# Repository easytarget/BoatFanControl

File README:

# Humidity sensor and fan controller for a small boat
## By Owen.

* DigiSpark Based
 * ATTiny 85
 * Has a onboard 5v regulator
 * 6 IO pins.. very little extra cruft
 * Somewhat tricky to flash/develop for, Lack of a uart is a total pain during debug.
* PWM fan control via a mosfet
* Battery voltage sensing for powersave and shutdown
* A button.. to allow on/off/quiet, etc.
* DHT11 Temperature and Humidity sensor
 * Not ideal, something more accurate would be prefered but this is what I have,

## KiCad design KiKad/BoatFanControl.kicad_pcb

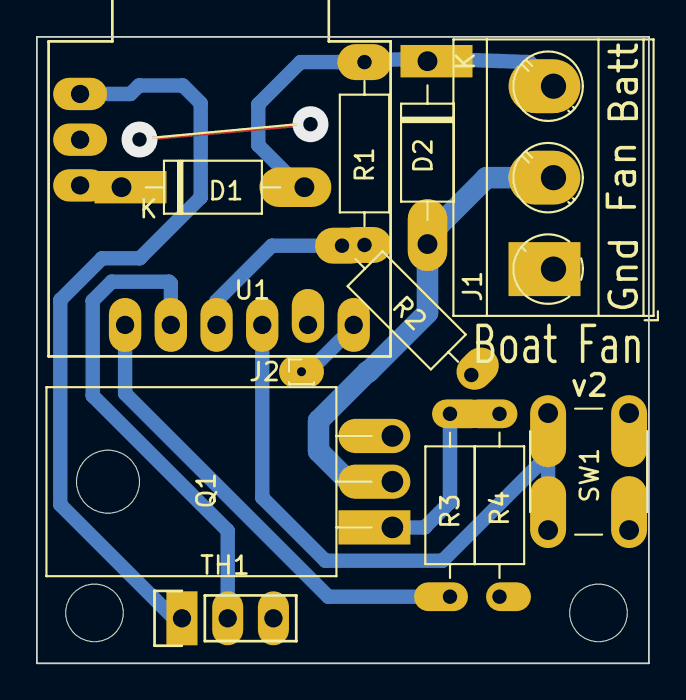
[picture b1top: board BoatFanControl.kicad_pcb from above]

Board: 2 copper layers, 34.0 x 34.8 mm, 14 parts (0 on the bottom side), 11 nets.

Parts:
D1, D2: 1N4007; D_DO-41_SOD81_P10.16mm_Horizontal
H1, H2: MountingHole; MountingHole_3.2mm_M3
J1: Batt; TerminalBlock_MetzConnect_Type073_RT02603HBLU_1x03_P5.08mm_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
J2: Reset; PinHeader_1x01_P1.00mm_Vertical
Q1: IRLZ14; TO-220F-3_Horizontal_TabDown
R1, R4: 10K; R_Axial_DIN0207_L6.3mm_D2.5mm_P10.16mm_Horizontal
R2: 1K; R_Axial_DIN0207_L6.3mm_D2.5mm_P10.16mm_Horizontal
R3: 220R; R_Axial_DIN0207_L6.3mm_D2.5mm_P10.16mm_Horizontal
SW1: SW_Push; SW_PUSH_6mm
TH1: DHT11; DHT11_Temperature_Humidity
U1: Digispark

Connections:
+5V: TH1.1, U1.9
DHT11: TH1.2, U1.2
FAN-GND: D2.2, J1.2, Q1.2
GND: J1.1, Q1.3, R2.2, R4.2, SW1.1, TH1.3, U1.8
unnamed: Q1.1, R3.2, R4.1
Reset: J2.1, U1.6
Vbatt: D1.2, D2.1, J1.3, R1.1
Vin: D1.1, U1.7
Vsense: R1.2, R2.1, U1.3
button: SW1.2, U1.4
fan-pwm: R3.1, U1.1

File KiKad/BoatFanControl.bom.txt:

"Source:","/home/owen/Circuits/BoatFanControl/KiKad/BoatFanControl.sch"
"Date:","Mon 22 Jun 2020 17:11:08 CEST"
"Tool:","Eeschema 5.1.6-1.fc32"
"Generator:","/usr/share/kicad/plugins/bom_csv_grouped_by_value.py"
"Component Count:","14"

"Individual Components:"

"Item","Qty","Reference(s)","Value","LibPart","Footprint","Datasheet","Description","Manufacturer","Pricing"
"","","D1","1N4007","Diode:1N4007","Diode_THT:D_DO-41_SOD81_P10.16mm_Horizontal","http://www.vishay.com/docs/88503/1n4001.pdf","","",""
"","","D2","1N4007","Diode:1N4007","Diode_THT:D_DO-41_SOD81_P10.16mm_Horizontal","http://www.vishay.com/docs/88503/1n4001.pdf","","",""
"","","H1","MountingHole","Mechanical:MountingHole","MountingHole:MountingHole_3.2mm_M3","~","","",""
"","","H2","MountingHole","Mechanical:MountingHole","MountingHole:MountingHole_3.2mm_M3","~","","",""
"","","J1","Batt","Connector:Screw_Terminal_01x03","TerminalBlock_MetzConnect:TerminalBlock_MetzConnect_Type073_RT02603HBLU_1x03_P5.08mm_Horizontal","~","","",""
"","","J2","Reset","Connector_Generic:Conn_01x01","Connector_PinHeader_1.00mm:PinHeader_1x01_P1.00mm_Vertical","~","","",""
"","","Q1","IRLZ14","Transistor_FET:IRLIZ44N","Package_TO_SOT_THT:TO-220F-3_Horizontal_TabDown","http://www.irf.com/product-info/datasheets/data/irliz44n.pdf","","",""
"","","R1","10K","Device:R","Resistor_THT:R_Axial_DIN0207_L6.3mm_D2.5mm_P10.16mm_Horizontal","~","","",""
"","","R2","1K","Device:R","Resistor_THT:R_Axial_DIN0207_L6.3mm_D2.5mm_P10.16mm_Horizontal","~","","",""
"","","R3","220R","Device:R","Resistor_THT:R_Axial_DIN0207_L6.3mm_D2.5mm_P10.16mm_Horizontal","~","","",""
"","","R4","10K","Device:R","Resistor_THT:R_Axial_DIN0207_L6.3mm_D2.5mm_P10.16mm_Horizontal","~","","",""
"","","SW1","SW_Push","Switch:SW_Push","Button_Switch_THT:SW_PUSH_6mm","~","","",""
"","","TH1","DHT11","sensorz:DHT11_Temperature_Humidity","sensorz:DHT11_Temperature_Humidity","","","",""
"","","U1","Digispark","mcuz:Digispark","mcuz:Digispark","","Digispark Microcontroller","Digistump","0.00@0"



"Collated Components:"

"Item","Qty","Reference(s)","Value","LibPart","Footprint","Datasheet","Description","Manufacturer","Pricing"
"1","2","D1, D2","1N4007","Diode:1N4007","Diode_THT:D_DO-41_SOD81_P10.16mm_Horizontal","http://www.vishay.com/docs/88503/1n4001.pdf","","",""
"2","2","H1, H2","MountingHole","Mechanical:MountingHole","MountingHole:MountingHole_3.2mm_M3","~","","",""
"3","1","J1","Batt","Connector:Screw_Terminal_01x03","TerminalBlock_MetzConnect:TerminalBlock_MetzConnect_Type073_RT02603HBLU_1x03_P5.08mm_Horizontal","~","","",""
"4","1","J2","Reset","Connector_Generic:Conn_01x01","Connector_PinHeader_1.00mm:PinHeader_1x01_P1.00mm_Vertical","~","","",""
"5","1","Q1","IRLZ14","Transistor_FET:IRLIZ44N","Package_TO_SOT_THT:TO-220F-3_Horizontal_TabDown","http://www.irf.com/product-info/datasheets/data/irliz44n.pdf","","",""
"6","2","R1, R4","10K","Device:R","Resistor_THT:R_Axial_DIN0207_L6.3mm_D2.5mm_P10.16mm_Horizontal","~","","",""
"7","1","R2","1K","Device:R","Resistor_THT:R_Axial_DIN0207_L6.3mm_D2.5mm_P10.16mm_Horizontal","~","","",""
"8","1","R3","220R","Device:R","Resistor_THT:R_Axial_DIN0207_L6.3mm_D2.5mm_P10.16mm_Horizontal","~","","",""
"9","1","SW1","SW_Push","Switch:SW_Push","Button_Switch_THT:SW_PUSH_6mm","~","","",""
"10","1","TH1","DHT11","sensorz:DHT11_Temperature_Humidity","sensorz:DHT11_Temperature_Humidity","","","",""
"11","1","U1","Digispark","mcuz:Digispark","mcuz:Digispark","","Digispark Microcontroller","Digistump","0.00@0"

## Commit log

2019-08-27 Initial; circuit done, based off of the solar light controller
2019-08-28 Updated with seperate DHT11 mount
2019-08-29 New Code; work in progress
2019-08-29 Lets ignore more stuff!
2019-08-29 Some documentation
2019-08-29 Lets get some Markup
2019-08-29 Notes and images
2019-08-29 Piccies
2019-08-29 Editz
2019-08-29 Notes
2019-08-30 Case, make PCB square..
2019-09-03 High speed PWM and led control
2019-09-03 Case Mods
2019-09-18 Add some demos so I can work on Interrupt routines
2019-09-18 Update for github markup
2019-09-18 Notes and queries
2019-09-30 Get the interrupt demos workimg
2019-09-30 Work on interrupt and test code
2020-06-06 Humm.. debug implemented, blows size up
2020-06-07 switch to DigiUSB for debug
2020-06-07 DigiUSB debug works, sensor often fails
2020-06-08 Checkpoint, working voltage calibrator
2020-06-08 Working test and calibration programs usinf DigiUSB for comms
2020-06-08 rename VCC to VIN
2020-06-09 Nicely working sensor calibrator and tester, using DigiUSB
2020-06-09 Work in progress
2020-06-11 further developed
2020-06-12 button wrangler part 1
2020-06-12 Very close to final; needs proportional fan in high mode
2020-06-12 Trivial timing and UI bits
2020-06-13 test tool speedup
2020-06-13 Move to 5 readings instead of 10
2020-06-16 RC1: functionally complete and tested. To be installed.
2020-06-18 Refactor following release; this will be r1.1
2020-06-18 Readme update
2020-06-22 Update Comments and readme's
2020-06-22 PCB work, add flyback diode
2020-06-22 New schematic
2020-06-26 Trivial comments
2020-06-26 New combined interrupt demo. Works!
2020-06-26 Starting on interrupt sleep between reaings, lower power consumption ehen fan off Debug/DigiUSB has been stripped out, no longer necesscary Sleep setup routines are imported. Still need implementing 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
2020-06-26 Baby Steps
2020-06-26 Declutter, example from DHT lib no longer needed
2020-06-26 Remove devel mode reference from comments
2020-06-29 Test of how to run main loop using interrupts
2020-07-01 Sleep mode in between readings when fan is off, lower power
2020-07-03 iSome better pictures taken when upgrading the installed unit
2020-07-03 ReadMe changes
2020-07-03 more doc updates
2020-07-03 more documentation
2020-07-03 Refresh the PCB
